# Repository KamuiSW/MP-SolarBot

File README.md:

# Solar Panel Cleaning Robot

This is the code and hardware files for our 6VWO profielwerkstuk. The project is about a small robot that can map a solar panel, plan a path over it, and detect dirty spots.

## Parts of the project

### 1. Firmware
Language: C++ <br>
Hardware: Raspberry Pi <br><br>
What it does:<br>
Motor control <br>
Edge detection with sensors<br>
Mapping the panel<br>
Navigation over the mapped area<br><br>
Compilation:<br>
    ```g++ main.cpp mapping.cpp navigation.cpp executor.cpp stains.cpp stain_planner.cpp -o robot_core -lwiringPi -std=c++17
    ```

### 2. Web interface and simulation
Backend: Python<br>
Frontend: HTML5<br><br>
The web interface shows the robot position, the path, and detected stains. There is also a Python simulation so we can test the logic without always using the real robot.<br>

## Simulation

1.  Install dependencies:
    ```bash
    pip install fastapi uvicorn websockets
    ```

2.  Run the server:
    ```bash
    python Software\src\Simulation\server.py
    ```

3.  Open the UI:
    Open `http://localhost:8000` in your web browser.

4.  Start the simulation:
Click "Start Simulation".<br>

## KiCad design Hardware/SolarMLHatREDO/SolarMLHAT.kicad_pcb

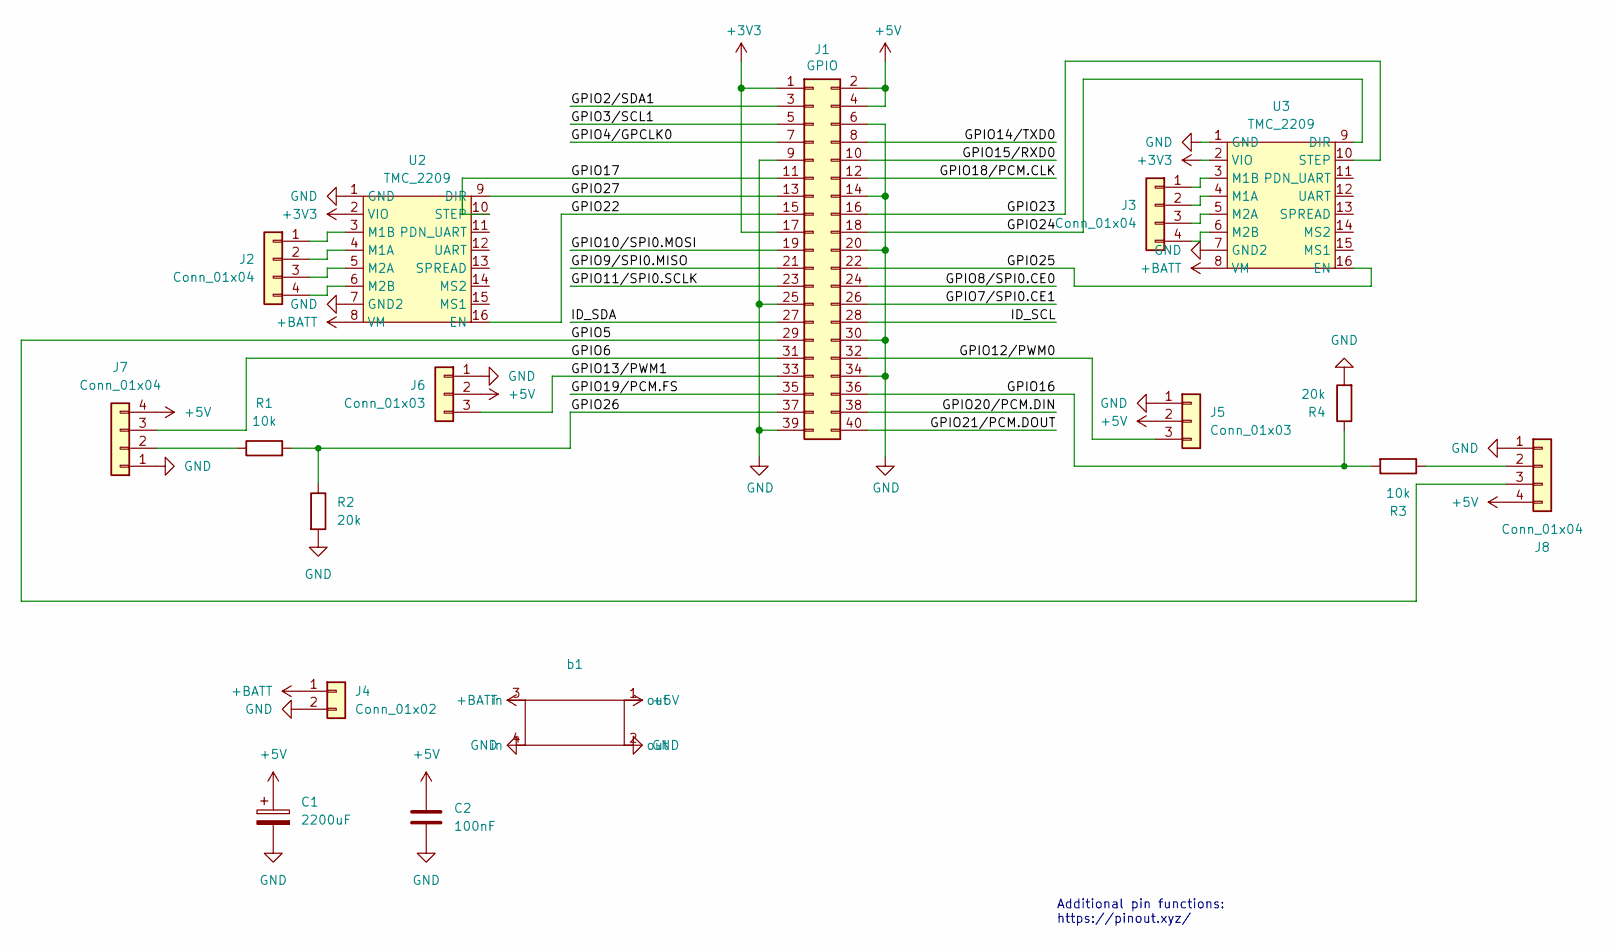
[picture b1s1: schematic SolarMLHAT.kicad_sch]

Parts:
C1: 2200uF; CP_Radial_D10.0mm_P5.00mm
C2: 100nF; C_1206_3216Metric_Pad1.33x1.80mm_HandSolder
J1: GPIO; PinSocket_2x20_P2.54mm_Vertical
J2, J3: Conn_01x04; JST_PH_B4B-PH-K_1x04_P2.00mm_Vertical
J4: Conn_01x02; TerminalBlock_MaiXu_MX126-5.0-02P_1x02_P5.00mm
J5, J6: Conn_01x03; PinHeader_1x03_P2.54mm_Vertical
J7, J8: Conn_01x04; PinHeader_1x04_P2.54mm_Vertical
R1, R3: 10k; R_1206_3216Metric_Pad1.30x1.75mm_HandSolder
R2, R4: 20k; R_1206_3216Metric_Pad1.30x1.75mm_HandSolder
U2, U3: TMC_2209; TMC_2209_v985
b1: XL4015 5A SizeM

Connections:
+3V3: J1.1, J1.17, U2.2 (VIO), U3.2 (VIO)
+5V: C1.1, C2.1, J1.2, J1.4, J5.2, J6.2, J7.4, J8.4, b1.1 (out)
+BATT: J4.1, U2.8 (VM), U3.8 (VM), b1.3 (in)
/GPIO2/SDA1: J1.3
/GPIO3/SCL1: J1.5
/GPIO4/GPCLK0: J1.7
/GPIO5: J1.29, J8.3
/GPIO6: J1.31, J7.3
/GPIO7/SPI0.CE1: J1.26
/GPIO8/SPI0.CE0: J1.24
/GPIO9/SPI0.MISO: J1.21
/GPIO10/SPI0.MOSI: J1.19
/GPIO11/SPI0.SCLK: J1.23
/GPIO12/PWM0: J1.32, J5.3
/GPIO13/PWM1: J1.33, J6.3
/GPIO14/TXD0: J1.8
/GPIO15/RXD0: J1.10
/GPIO16: J1.36, R3.2, R4.1
/GPIO17: J1.11, U2.10 (STEP)
/GPIO18/PCM.CLK: J1.12
/GPIO19/PCM.FS: J1.35
/GPIO20/PCM.DIN: J1.38
/GPIO21/PCM.DOUT: J1.40
/GPIO22: J1.15, U2.16 (EN)
/GPIO23: J1.16, U3.10 (STEP)
/GPIO24: J1.18, U3.9 (DIR)
/GPIO25: J1.22, U3.16 (EN)
/GPIO26: J1.37, R1.2, R2.1
/GPIO27: J1.13, U2.9 (DIR)
/ID_SCL: J1.28
/ID_SDA: J1.27
GND: C1.2, C2.2, J1.6, J1.9, J1.14, J1.20, J1.25, J1.30, J1.34, J1.39, J4.2, J5.1, J6.1, J7.1, J8.1, R2.2, R4.2, U2.1 (GND), U2.7 (GND2), U3.1 (GND), U3.7 (GND2), b1.2 (out), b1.4 (in)
unnamed: J2.1, U2.3 (M1B)
unnamed: J2.2, U2.4 (M1A)
unnamed: J2.3, U2.5 (M2A)
unnamed: J2.4, U2.6 (M2B)
unnamed: J3.1, U3.3 (M1B)
unnamed: J3.2, U3.4 (M1A)
unnamed: J3.3, U3.5 (M2A)
unnamed: J3.4, U3.6 (M2B)
unnamed: J7.2, R1.1
unnamed: J8.2, R3.1

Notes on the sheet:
Additional pin functions: https://pinout.xyz/

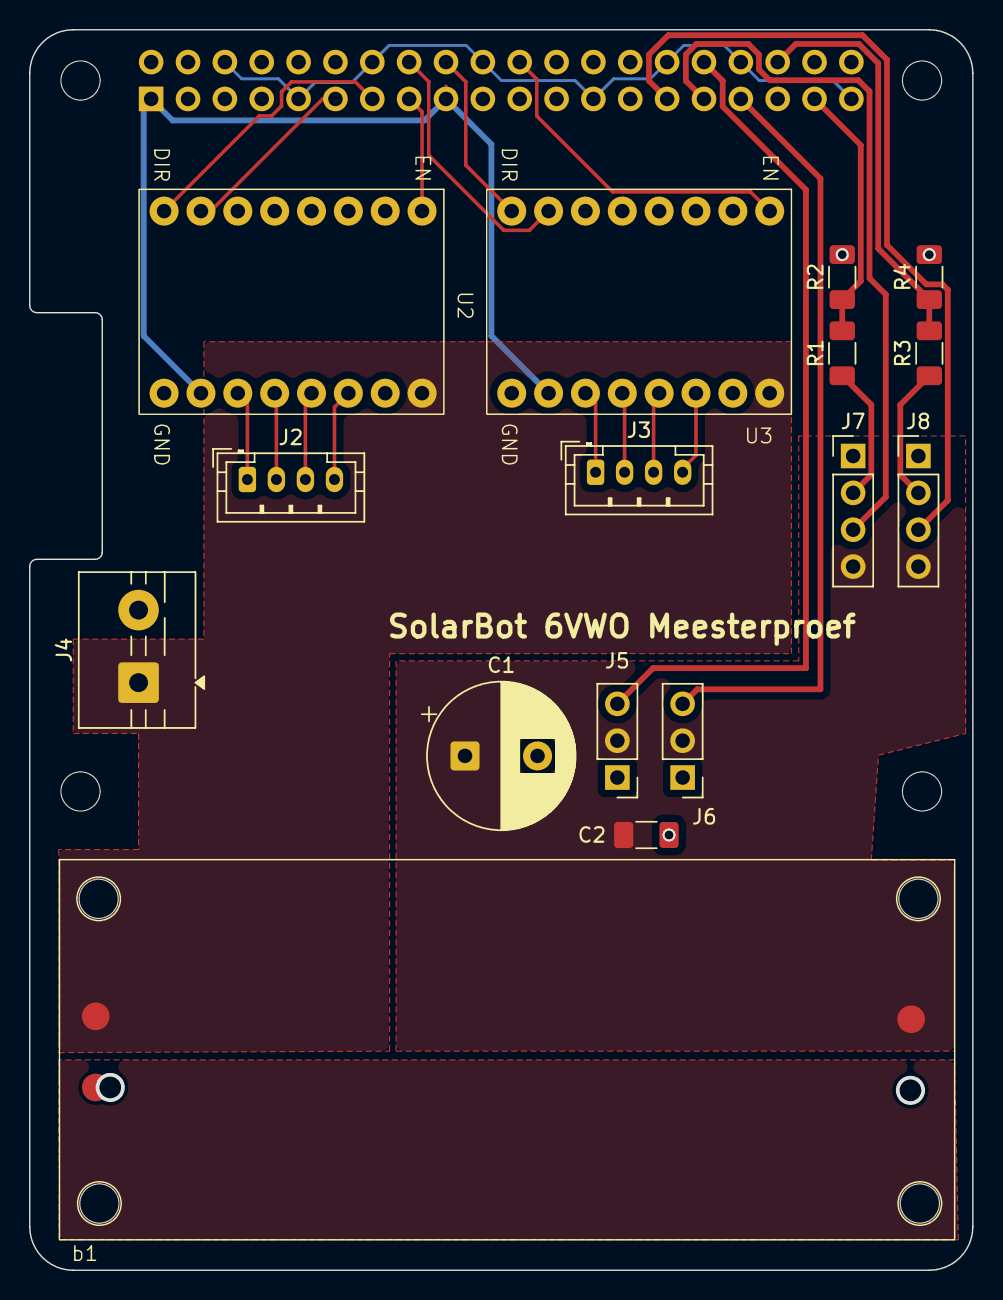
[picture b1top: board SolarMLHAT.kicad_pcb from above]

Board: 2 copper layers, 65.0 x 85.5 mm, 21 parts (1 on the bottom side), 26 nets.

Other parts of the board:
MH1, MH2, MH3, MH4: MountingHole_2.7mm_M2.5

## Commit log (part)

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2025-11-20 ML references added
2025-11-20 mapping and simulator
2025-11-25 Detection python
2025-11-25 Update Dataset file path
2025-11-25 filepathchange
2025-11-25 Created "Dirty" subfolder
2025-11-25 Dataset_root modification
2025-11-26 robotcontrolls
2025-12-18 Panel_mask.py addition
2025-12-18 small note on tile evaluation
2025-12-18 robot_motion done
2025-12-18 fixed errors
2025-12-20 Heatmap_demo change image
2026-01-14 Files Cleaned
2026-01-22 added web and simulation
2026-01-23 finished simulation and used the simulation to fix actual problems
2026-01-26 Add SolarMLHAT PCB design files and assets
    Initial commit of SolarMLHAT hardware design files, including KiCad project files, Gerber outputs, fabrication data, and design backups. Also adds a new asset to the simulation software.
2026-01-27 run_demo file path change
2026-01-28 Folder Structure adjustment
2026-01-28 File path edit
2026-01-29 modification method comparison
2026-02-09 added robot back forth testing
2026-02-11 math explination
2026-02-12 recalibration
2026-02-12 demo run
2026-02-12 file path modification
2026-04-22 lsat
2026-06-16 Revise README for clarity and formatting
    Updated README to simplify language and formatting.
